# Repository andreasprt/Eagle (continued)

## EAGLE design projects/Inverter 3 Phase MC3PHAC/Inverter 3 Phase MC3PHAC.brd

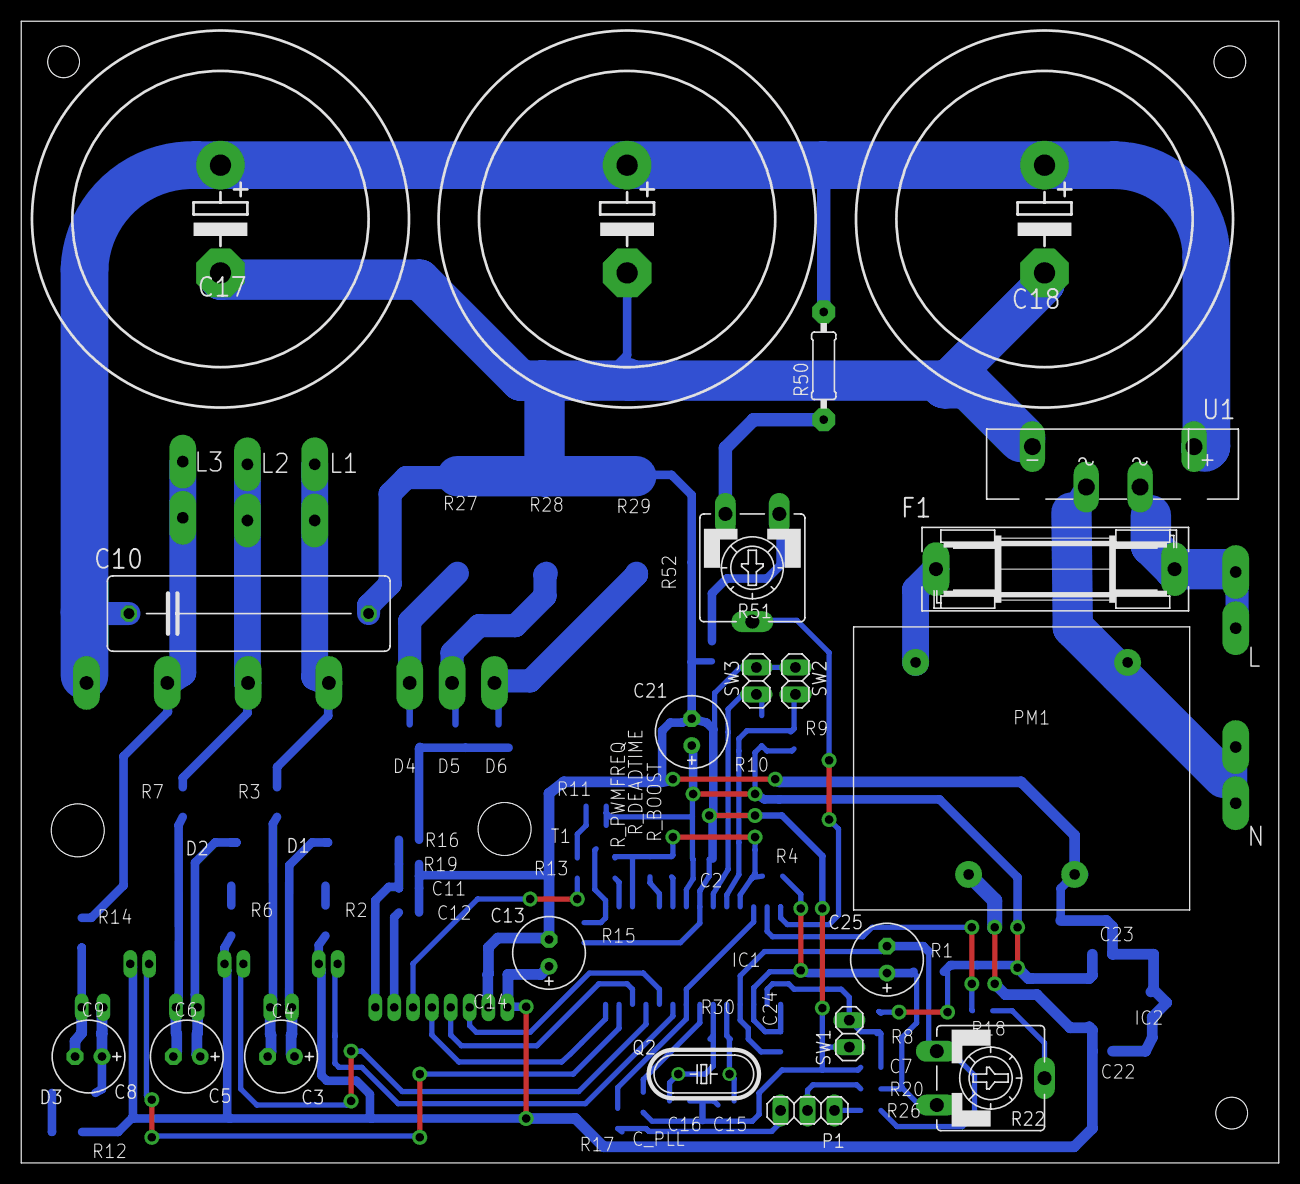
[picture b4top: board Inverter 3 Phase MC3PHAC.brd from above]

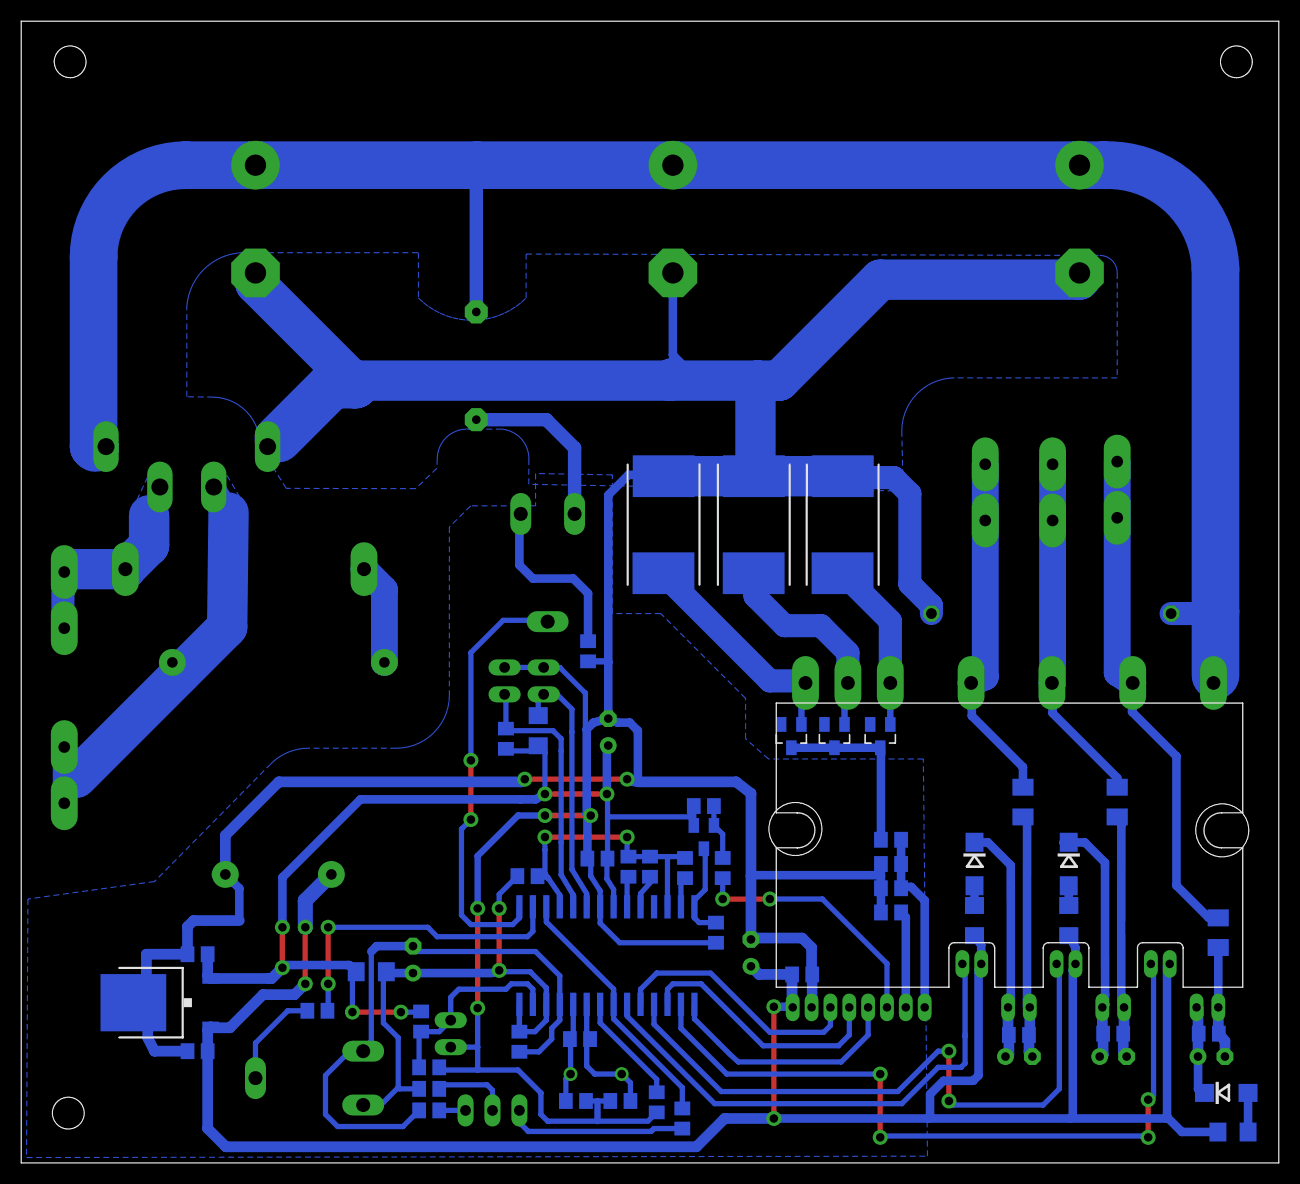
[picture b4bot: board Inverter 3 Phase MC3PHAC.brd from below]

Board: 2 copper layers, 118.6 x 107.7 mm, 78 parts (52 on the bottom side), 55 nets.

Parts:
C2, C4, C6, C7, C9, C12, C14, C22, C23, C24: 100n; C0805
C3, C5, C8, C13: 100u; E2,5-7
C10: 0.1u; C225-074X268
C11: 1n; C0805
C15, C16: 22p; C0805
C17, C18, C19: 470u; EB35D
C21: 10u; E2,5-7
C25: 1u; E2,5-7
C_PLL: 100n; C0805
D1, D2, D3: ER1J; DO214AC
D4, D5, D6: BAR43; SOT23
F1: T1A; SH22,5
IC1: MC3PHAC; SO28W
IC2: 7805DT; TO252
L, L1, L2, L3: PIN2F061.060; F061.060
N: PIN2F061.060; F061.060
P1: 5k; 1X03
PM1: MYRRA 47155; MYRRA
Q2: 4.0MHz; HC49U-V
R1: 2R; R1206
R2, R6, R12: 20R; R1206
R3, R7, R14: 5R6; M1206
R4: 6.8k; R0805
R8, R9, R15, R52: 10k; R0805
R10: 10k; R1206
R11: 6k8; R0805
R13: 22k; R0805
R16: 1k; R0805
R17, R18: 4.7k; R0805
R19: 47k; R0805
R20: 2k2; R0805
R22, R51: 4k7; CA9V
R26: 150R; R0805
R27, R28, R29: 0R082 5W; WSC4527
R30: 10M; R0805
R50: 1M; 0207/10
R_BOOST: 2k2; R0805
R_DEADTIME: 1k8; R0805
R_PWMFREQ: 3k9; R0805
SPM1: FSBS10CH60; SPM27-BA
SW1: RESET; 1X02
SW2: START; 1X02
SW3: FOR/REW; 1X02
T1: BC858; SOT23-BEC
U1: KBU8G; KBU

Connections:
+5V: C2.2, C21.+, C23.2, IC1.21, IC2.2, R1.2, R8.1, R9.1, R10.1, R11.1, T1.E
+15V: C13.+, C14.2, C22.2, IC2.1, PM1.7, R2.1, R6.1, R12.1, SPM1.1, SPM1.10, SPM1.14, SPM1.18
DC_BUS: C10.1, C17.+, C18.+, C19.+, R50.2, SPM1.27, U1.+
GND: C2.1, C7.2, C10.2, C11.1, C12.1, C13.-, C14.1, C15.1, C16.1, C17.-, C18.-, C19.-, C21.-, C22.1, C23.1, C_PLL.2, IC1.22, IC2.3, PM1.9, R15.2, R19.2, R27.1, R28.1, R29.1, R52.2, SPM1.2, SW1.1, SW2.1, SW3.1, U1.-
GND1: C24.1, C25.-, IC1.4, R22.A, R26.2
unnamed: C_PLL.1, IC1.7
unnamed: R18.2, R22.S
unnamed: IC1.16, R_PWMFREQ.2
unnamed: IC1.19, R_DEADTIME.2
unnamed: IC1.20, R_BOOST.2
unnamed: IC1.17, IC1.25, R4.1, R_BOOST.1, R_DEADTIME.1, R_PWMFREQ.1
unnamed: IC1.8, IC1.26, R17.1
unnamed: P1.3, R17.2
unnamed: C15.2, IC1.5, Q2.2, R30.2
unnamed: P1.2, R20.2
unnamed: IC1.27, R18.1
unnamed: IC1.24, R9.2, SW2.2
unnamed: IC1.23, R10.2, SW3.2
unnamed: C16.2, IC1.6, Q2.1, R30.1
unnamed: C7.1, IC1.2, R8.2, SW1.2
unnamed: N.A1, PM1.1, U1.AC2
unnamed: C5.-, C6.2, R7.2, SPM1.16
unnamed: F1.2, PM1.5
unnamed: F1.1, L.A1, U1.AC1
unnamed: R51.A, R52.1
unnamed: C3.+, C4.1, D1.C, SPM1.11
unnamed: C3.-, C4.2, R3.2, SPM1.12
unnamed: D1.A, R2.2
unnamed: C11.2, R16.2, R19.1, SPM1.8
unnamed: IC1.15, R15.1, T1.C
unnamed: C12.2, SPM1.7
unnamed: C5.+, C6.1, D2.C, SPM1.15
unnamed: D2.A, R6.2
unnamed: C8.+, C9.1, D3.C, SPM1.19
unnamed: D3.A, R12.2
unnamed: C8.-, C9.2, R14.2, SPM1.20
unnamed: D4.1, R27.2, SPM1.23
unnamed: D5.1, R28.2, SPM1.22
unnamed: D6.1, R29.2, SPM1.21
unnamed: D4.3, D5.3, D6.3, R16.1
unnamed: R11.2, R13.1, T1.B
unnamed: P1.1, R26.1
unnamed: IC1.28, R51.S
PWM-U-BOT: IC1.10, SPM1.3
PWM-U-TOP: IC1.9, SPM1.9
PWM-V-BOT: IC1.12, SPM1.4
PWM-V-TOP: IC1.11, SPM1.13
PWM-W-BOT: IC1.14, SPM1.5
PWM-W-TOP: IC1.13, SPM1.17
S$1: R50.1, R51.E
U: L1.A1, R3.1, SPM1.24
V: L2.A1, R7.1, SPM1.25
VDD: C24.2, C25.+, IC1.1, IC1.3, R1.1, R4.2, R20.1, R22.E
V_FO: R13.2, SPM1.6
W: L3.A1, R14.1, SPM1.26

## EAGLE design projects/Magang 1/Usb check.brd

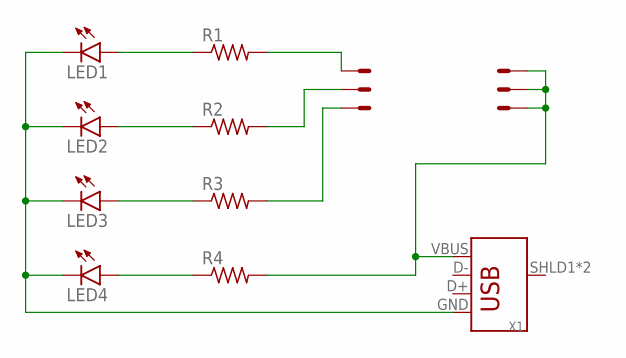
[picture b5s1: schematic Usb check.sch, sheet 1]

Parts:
LED1, LED2, LED3, LED4: LED5MM
R1, R2, R3, R4: R-US_0207/10; 0207/10
X1: USB_A_PTH_MALE; USB-A-H
X2, X3: 22-23-2031

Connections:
GND: LED1.K (C), LED2.K (C), LED3.K (C), LED4.K (C), X1.GND
unnamed: LED1.A, R1.1
unnamed: LED2.A, R2.1
unnamed: LED3.A, R3.1
unnamed: LED4.A, R4.1
unnamed: R1.2, X2.1
unnamed: R2.2, X2.2
unnamed: R3.2, X2.3
unnamed: R4.2, X1.VBUS, X3.1, X3.2, X3.3

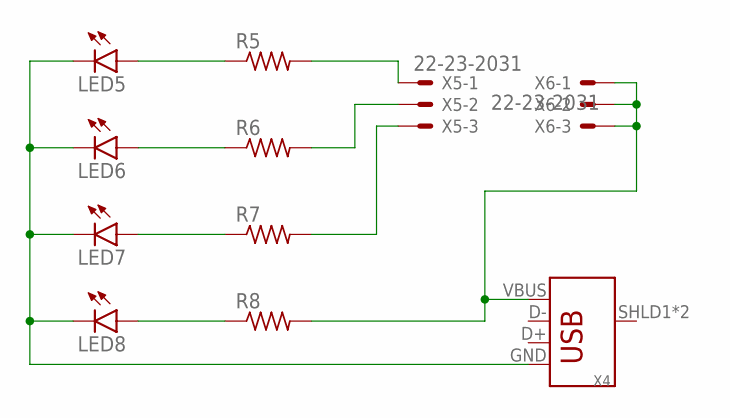
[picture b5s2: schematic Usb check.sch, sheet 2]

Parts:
LED5, LED6, LED7, LED8: LED5MM
R5, R6, R7, R8: R-US_0207/10; 0207/10
X4: USB_A_PTH_MALE; USB-A-H
X5, X6: 22-23-2031

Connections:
GND1: LED5.K (C), LED6.K (C), LED7.K (C), LED8.K (C), X4.GND
unnamed: LED5.A, R5.1
unnamed: LED6.A, R6.1
unnamed: LED7.A, R7.1
unnamed: LED8.A, R8.1
unnamed: R5.2, X5.1
unnamed: R6.2, X5.2
unnamed: R7.2, X5.3
unnamed: R8.2, X4.VBUS, X6.1, X6.2, X6.3

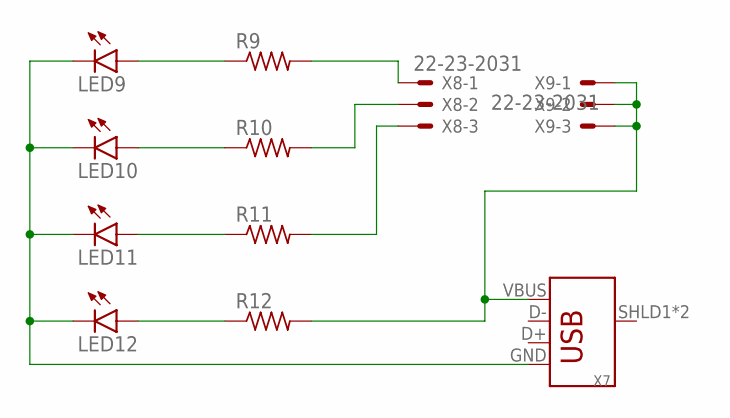
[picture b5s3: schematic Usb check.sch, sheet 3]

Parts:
LED9, LED10, LED11, LED12: LED5MM
R9, R10, R11, R12: R-US_0207/10; 0207/10
X7: USB_A_PTH_MALE; USB-A-H
X8, X9: 22-23-2031

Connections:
GND2: LED9.K (C), LED10.K (C), LED11.K (C), LED12.K (C), X7.GND
unnamed: LED9.A, R9.1
unnamed: LED10.A, R10.1
unnamed: LED11.A, R11.1
unnamed: LED12.A, R12.1
unnamed: R9.2, X8.1
unnamed: R10.2, X8.2
unnamed: R11.2, X8.3
unnamed: R12.2, X7.VBUS, X9.1, X9.2, X9.3

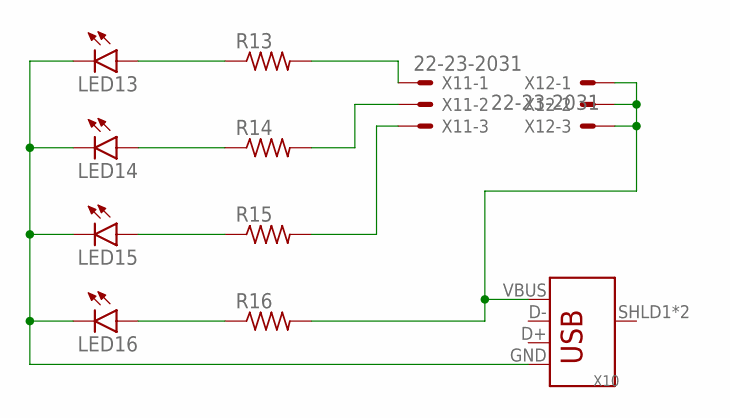
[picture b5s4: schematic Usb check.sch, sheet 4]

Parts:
LED13, LED14, LED15, LED16: LED5MM
R13, R14, R15, R16: R-US_0207/10; 0207/10
X10: USB_A_PTH_MALE; USB-A-H
X11, X12: 22-23-2031

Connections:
GND3: LED13.K (C), LED14.K (C), LED15.K (C), LED16.K (C), X10.GND
unnamed: LED13.A, R13.1
unnamed: LED14.A, R14.1
unnamed: LED15.A, R15.1
unnamed: LED16.A, R16.1
unnamed: R13.2, X11.1
unnamed: R14.2, X11.2
unnamed: R15.2, X11.3
unnamed: R16.2, X10.VBUS, X12.1, X12.2, X12.3

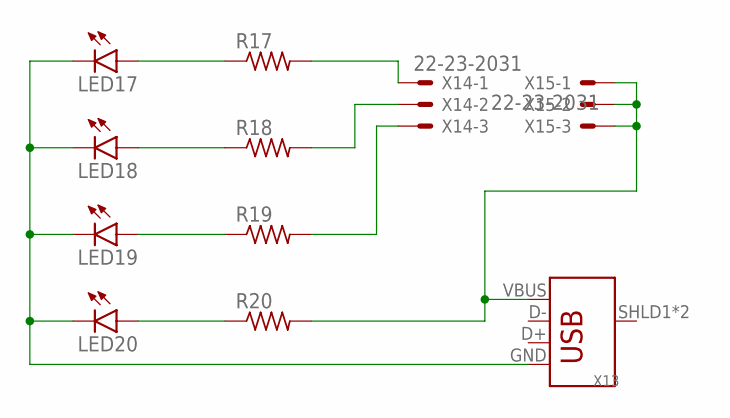
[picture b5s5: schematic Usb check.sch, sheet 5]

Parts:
LED17, LED18, LED19, LED20: LED5MM
R17, R18, R19, R20: R-US_0207/10; 0207/10
X13: USB_A_PTH_MALE; USB-A-H
X14, X15: 22-23-2031

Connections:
GND4: LED17.K (C), LED18.K (C), LED19.K (C), LED20.K (C), X13.GND
unnamed: LED17.A, R17.1
unnamed: LED18.A, R18.1
unnamed: LED19.A, R19.1
unnamed: LED20.A, R20.1
unnamed: R17.2, X14.1
unnamed: R18.2, X14.2
unnamed: R19.2, X14.3
unnamed: R20.2, X13.VBUS, X15.1, X15.2, X15.3

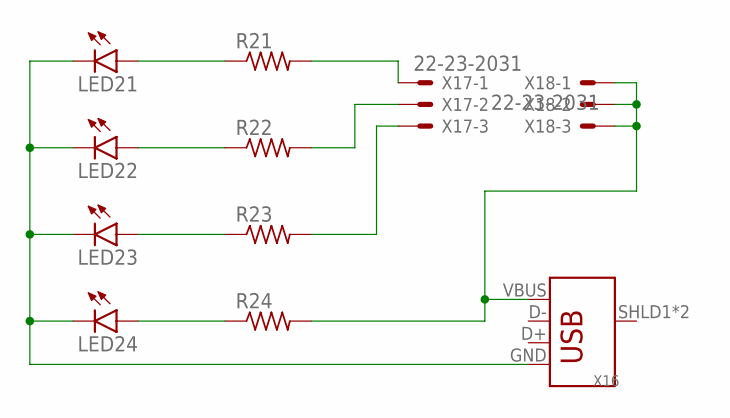
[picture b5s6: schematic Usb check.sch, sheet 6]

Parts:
LED21, LED22, LED23, LED24: LED5MM
R21, R22, R23, R24: R-US_0207/10; 0207/10
X16: USB_A_PTH_MALE; USB-A-H
X17, X18: 22-23-2031

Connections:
GND5: LED21.K (C), LED22.K (C), LED23.K (C), LED24.K (C), X16.GND
unnamed: LED21.A, R21.1
unnamed: LED22.A, R22.1
unnamed: LED23.A, R23.1
unnamed: LED24.A, R24.1
unnamed: R21.2, X17.1
unnamed: R22.2, X17.2
unnamed: R23.2, X17.3
unnamed: R24.2, X16.VBUS, X18.1, X18.2, X18.3

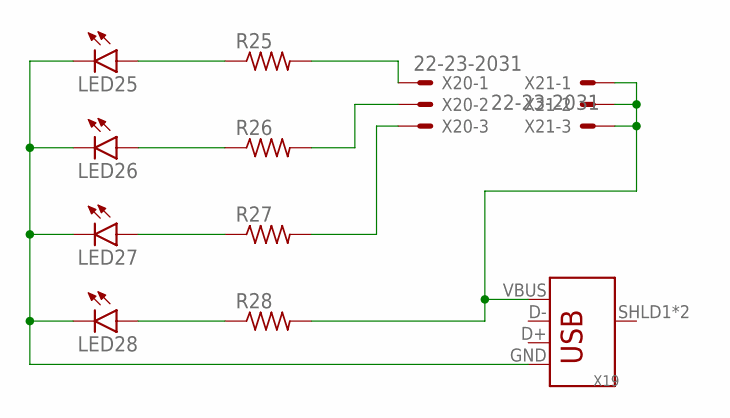
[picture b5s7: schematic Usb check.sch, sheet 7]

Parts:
LED25, LED26, LED27, LED28: LED5MM
R25, R26, R27, R28: R-US_0207/10; 0207/10
X19: USB_A_PTH_MALE; USB-A-H
X20, X21: 22-23-2031

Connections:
GND6: LED25.K (C), LED26.K (C), LED27.K (C), LED28.K (C), X19.GND
unnamed: LED25.A, R25.1
unnamed: LED26.A, R26.1
unnamed: LED27.A, R27.1
unnamed: LED28.A, R28.1
unnamed: R25.2, X20.1
unnamed: R26.2, X20.2
unnamed: R27.2, X20.3
unnamed: R28.2, X19.VBUS, X21.1, X21.2, X21.3

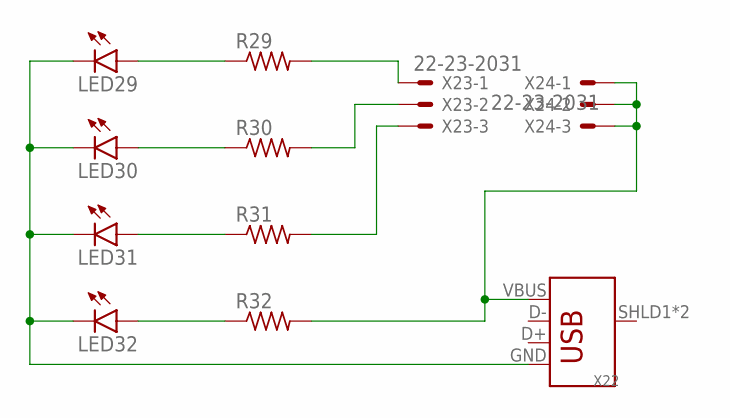
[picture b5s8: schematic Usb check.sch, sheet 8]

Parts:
LED29, LED30, LED31, LED32: LED5MM
R29, R30, R31, R32: R-US_0207/10; 0207/10
X22: USB_A_PTH_MALE; USB-A-H
X23, X24: 22-23-2031

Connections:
GND7: LED29.K (C), LED30.K (C), LED31.K (C), LED32.K (C), X22.GND
unnamed: LED29.A, R29.1
unnamed: LED30.A, R30.1
unnamed: LED31.A, R31.1
unnamed: LED32.A, R32.1
unnamed: R29.2, X23.1
unnamed: R30.2, X23.2
unnamed: R31.2, X23.3
unnamed: R32.2, X22.VBUS, X24.1, X24.2, X24.3

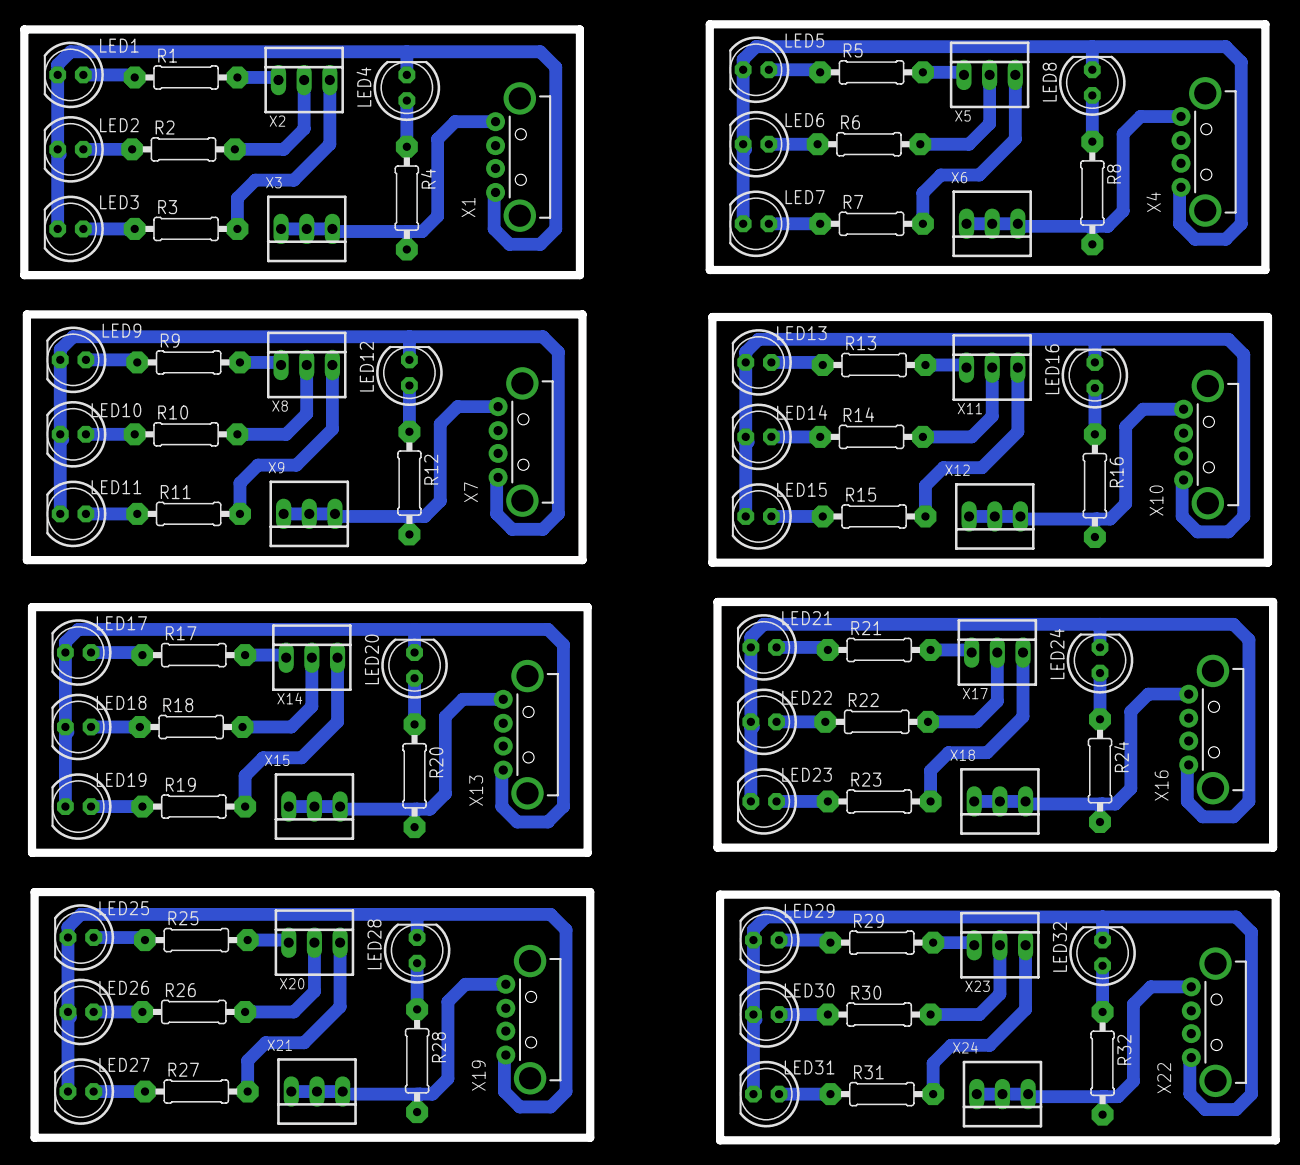
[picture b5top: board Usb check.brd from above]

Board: 2 copper layers, 123.8 x 110.4 mm, 88 parts (0 on the bottom side), 72 nets.

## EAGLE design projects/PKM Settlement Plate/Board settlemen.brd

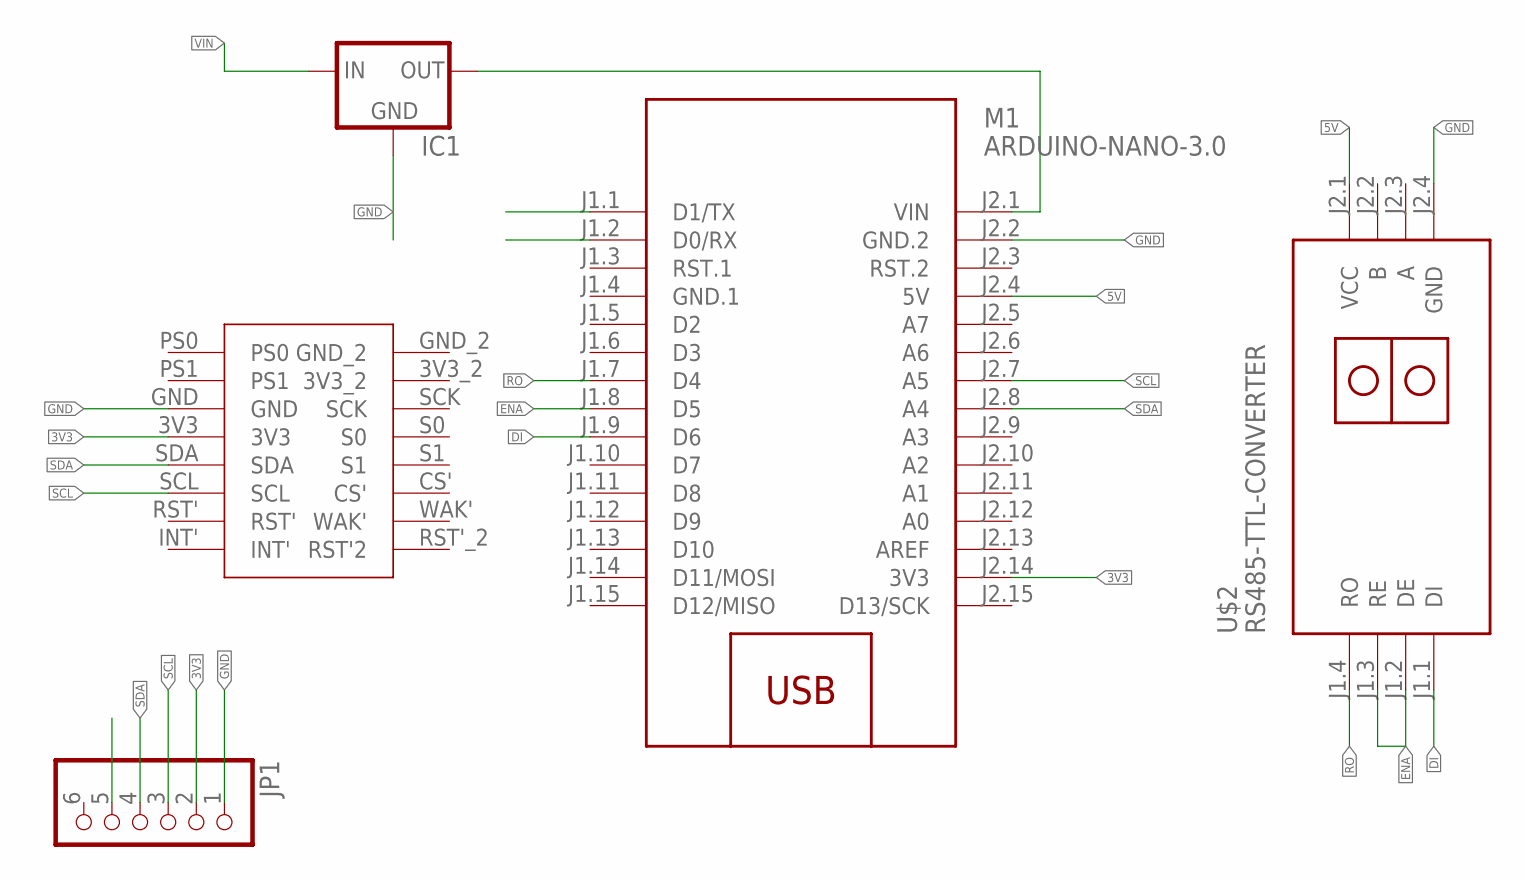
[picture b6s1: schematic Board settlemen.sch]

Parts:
IC1: 78MXXS
JP1: PINHD-1X6; 1X06
M1: ARDUINO-NANO-3.0
U$1: BNO080
U$2: RS485-TTL-CONVERTER

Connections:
3V3: JP1.2, M1.J2.14 (3V3), U$1.3V3
5V: M1.J2.4 (5V), U$2.J2.1 (VCC)
DI: M1.J1.9 (D6), U$2.J1.1 (DI)
ENA: M1.J1.8 (D5), U$2.J1.2 (DE), U$2.J1.3 (RE)
GND: IC1.GND, JP1.1, M1.J2.2 (GND.2), U$1.GND, U$2.J2.4 (GND)
GND.1: M1.J1.4 (GND.1)
unnamed: IC1.OUT, M1.J2.1 (VIN)
RO: M1.J1.7 (D4), U$2.J1.4 (RO)
SCL: JP1.3, M1.J2.7 (A5), U$1.SCL
SDA: JP1.4, M1.J2.8 (A4), U$1.SDA
VIN: IC1.IN

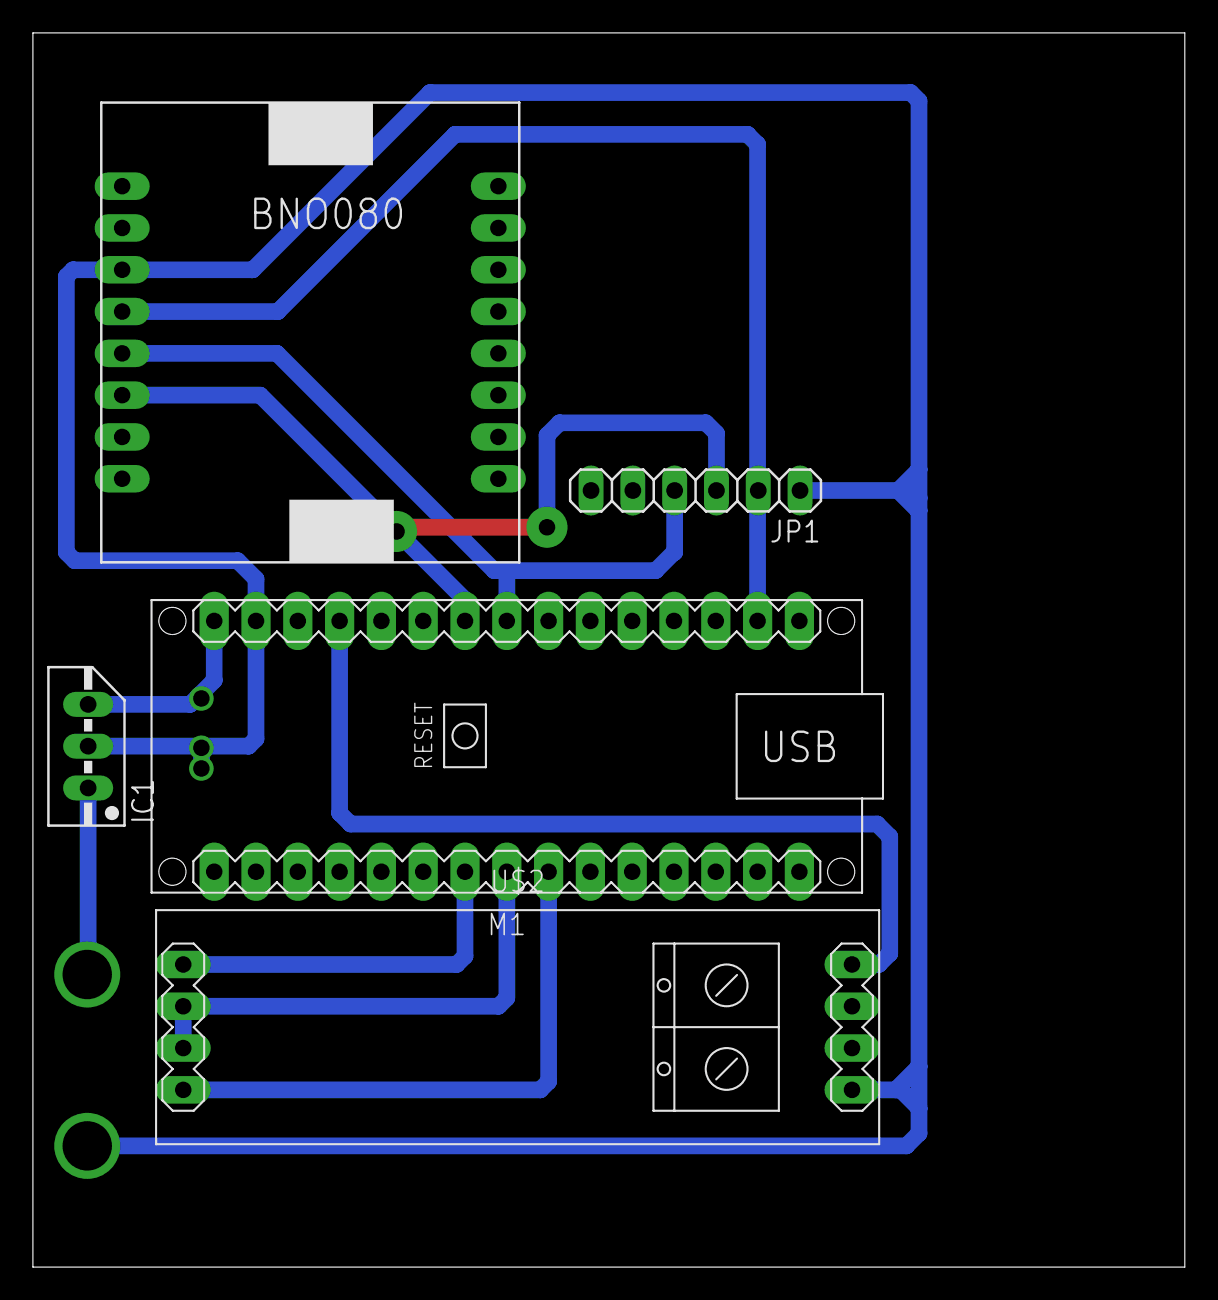
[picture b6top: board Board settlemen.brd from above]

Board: 2 copper layers, 70.0 x 75.0 mm, 5 parts (0 on the bottom side), 9 nets.

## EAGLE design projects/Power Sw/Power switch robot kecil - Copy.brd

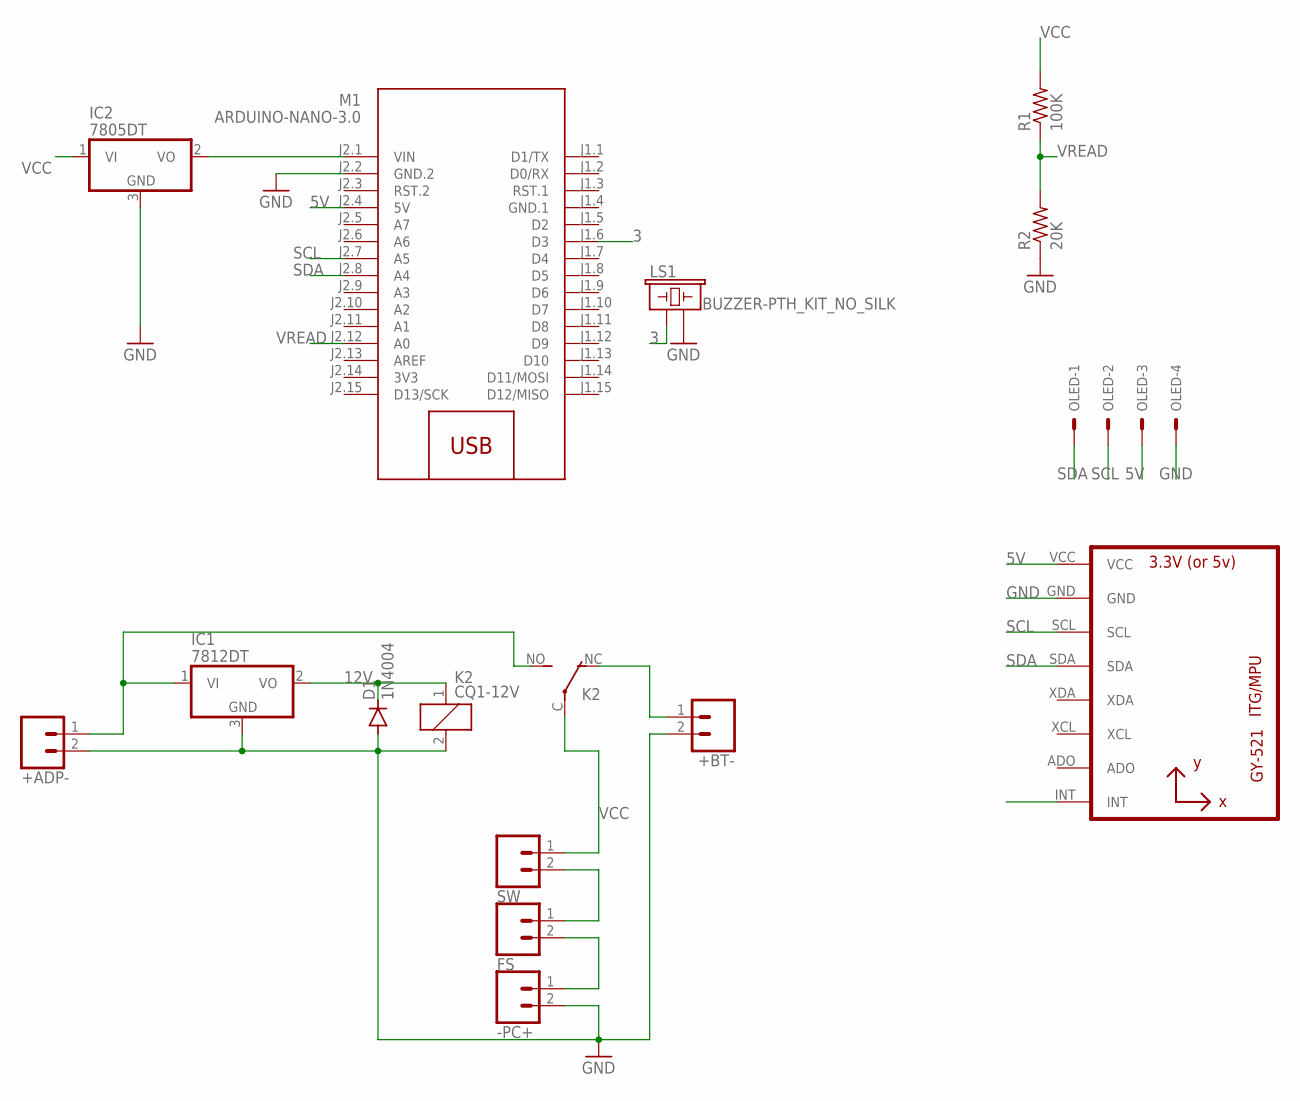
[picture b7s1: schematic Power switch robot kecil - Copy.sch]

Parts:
+ADP-: CONN_02LOCK_LONGPADS; 1X02_LOCK_LONGPADS
+BT-: CONN_02LOCK_LONGPADS; 1X02_LOCK_LONGPADS
-PC+: CONN_02LOCK_LONGPADS; 1X02_LOCK_LONGPADS
D1: 1N4004; DO41-10
FS: CONN_02LOCK_LONGPADS; 1X02_LOCK_LONGPADS
IC1: 7812DT; TO252
IC2: 7805DT; TO252
K2: CQ1-12V; CQ1
LS1: BUZZER-PTH_KIT_NO_SILK; BUZZER-12MM-NS-KIT
M1: ARDUINO-NANO-3.0
OLED: 22-27-2041-04; 6410-04
R1: 100K; 0207/10
R2: 20K; 0207/10
SW: CONN_02LOCK_LONGPADS; 1X02_LOCK_LONGPADS
U1: GY-521MPU6050; GY-521

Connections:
3: LS1.+ (1), M1.J1.6 (D3)
3V3: M1.J2.14 (3V3)
5V: M1.J2.4 (5V), OLED.3, U1.VCC
12V: D1.C, IC1.2 (VO), K2.1
GND: +ADP-.2, +BT-.2, -PC+.2, D1.A, IC1.3 (GND), IC2.3 (GND), K2.2, LS1.- (2), M1.J2.2 (GND.2), OLED.4, R2.1, U1.GND
GND.1: M1.J1.4 (GND.1)
unnamed: +ADP-.1, IC1.1 (VI), K2.NO (S)
unnamed: +BT-.1, K2.NC (O)
unnamed: -PC+.1, FS.2
unnamed: FS.1, SW.2
unnamed: IC2.2 (VO), M1.J2.1 (VIN)
SCL: M1.J2.7 (A5), OLED.2, U1.SCL
SDA: M1.J2.8 (A4), OLED.1, U1.SDA
VCC: IC2.1 (VI), K2.C, R1.2, SW.1
VREAD: M1.J2.12 (A0), R1.1, R2.2

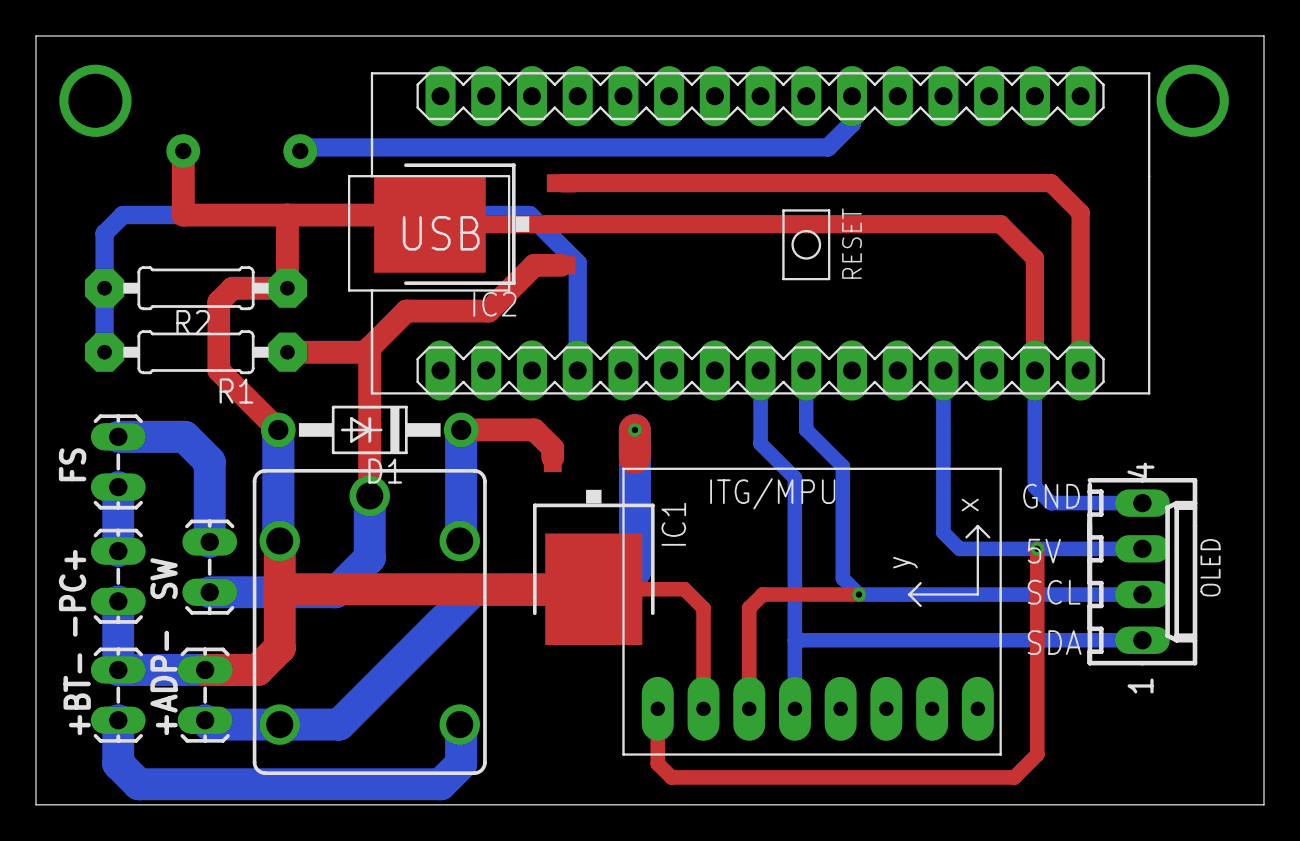
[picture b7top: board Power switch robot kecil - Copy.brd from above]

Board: 2 copper layers, 68.2 x 42.7 mm, 15 parts (0 on the bottom side), 13 nets.

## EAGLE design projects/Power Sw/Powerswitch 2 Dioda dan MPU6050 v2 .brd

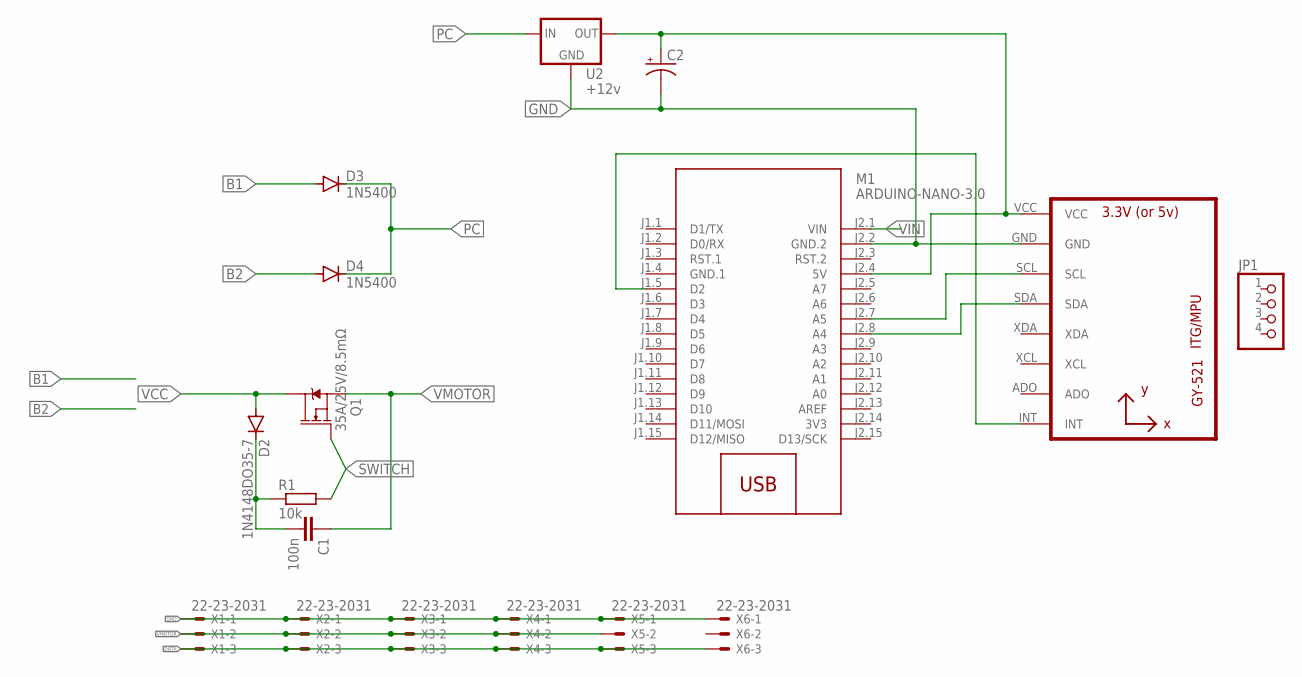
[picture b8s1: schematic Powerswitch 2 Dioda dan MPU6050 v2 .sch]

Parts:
C1: 100n; C025-030X050
C2: CPOL-USE2-5; E2-5
D2: 1N4148DO35-7; DO35-7
D3, D4: 1N5400; DO201-15
JP1: PINHD-1X4; 1X04
M1: ARDUINO-NANO-3.0
Q1: 35A/25V/8.5mΩ; DPAK
R1: 10k; R1206
U1: GY-521MPU6050; GY-521
U2: +12v; TO-252
X1, X2, X3, X4, X5, X6: 22-23-2031

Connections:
3V3: M1.J2.14 (3V3)
B1: D3.A
B2: D4.A
DATA: X1.3, X2.3, X3.3, X4.3, X5.3, X6.3
GND: C2.-, M1.J2.2 (GND.2), U1.GND, U2.3 (GND), X1.1, X2.1, X3.1, X4.1, X5.1, X6.1
GND.1: M1.J1.4 (GND.1)
unnamed: M1.J2.8 (A4), U1.SDA
unnamed: C1.2, D2.C, R1.1
unnamed: M1.J2.7 (A5), U1.SCL
unnamed: M1.J1.5 (D2), U1.INT
unnamed: C2.+, M1.J2.4 (5V), U1.VCC, U2.2 (OUT)
PC: D3.C, D4.C, U2.1 (IN)
SWITCH: Q1.1 (G), R1.2
VCC: D2.A, Q1.4 (D)
VIN: M1.J2.1 (VIN)
VMOTOR: C1.1, Q1.3 (S), X1.2, X2.2, X3.2, X4.2, X5.2

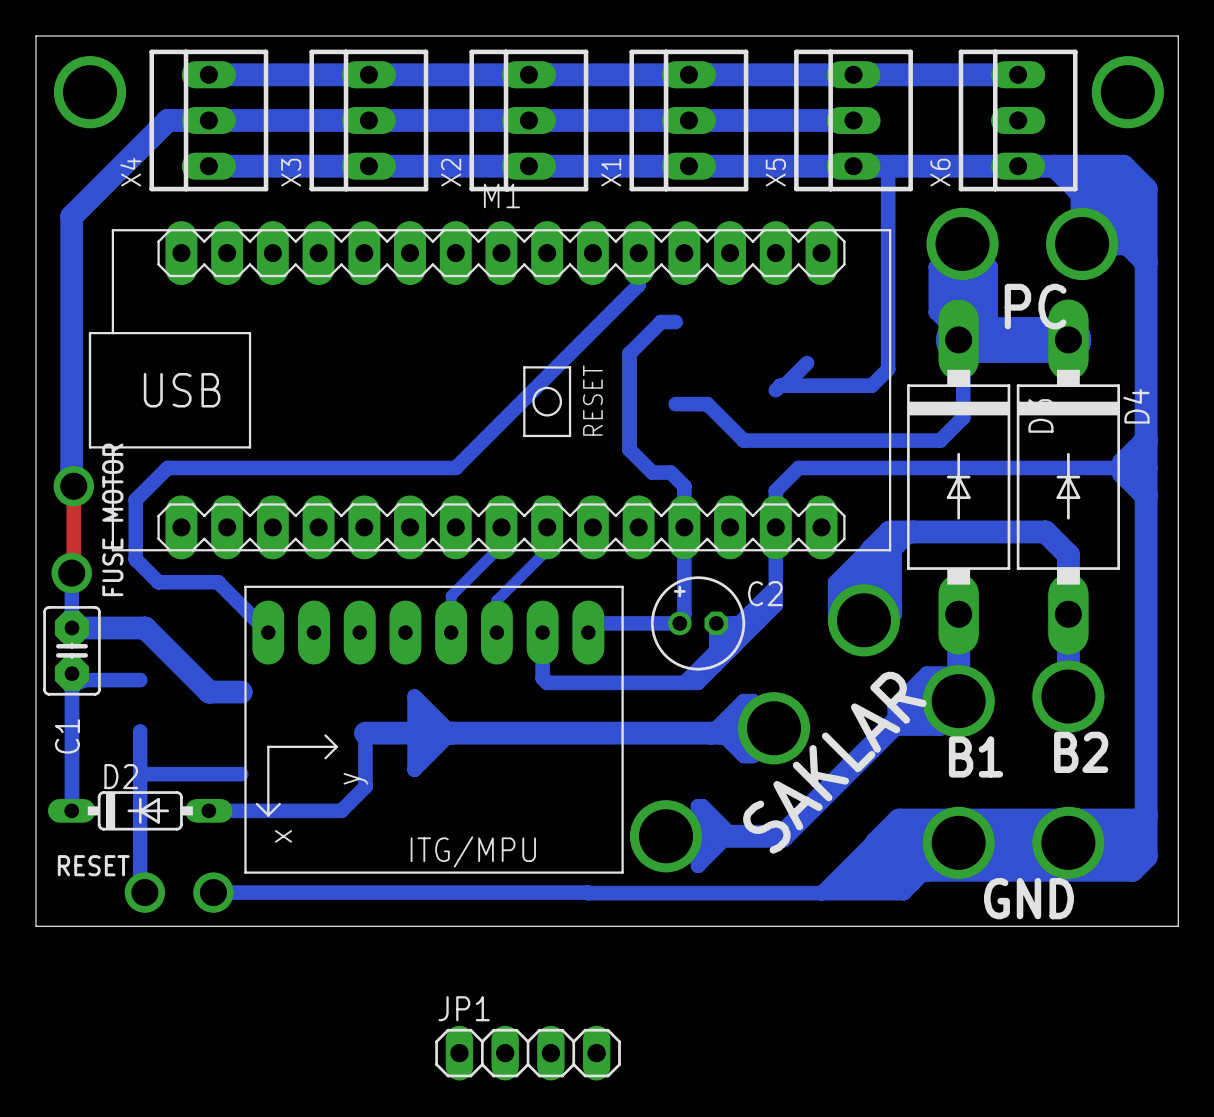
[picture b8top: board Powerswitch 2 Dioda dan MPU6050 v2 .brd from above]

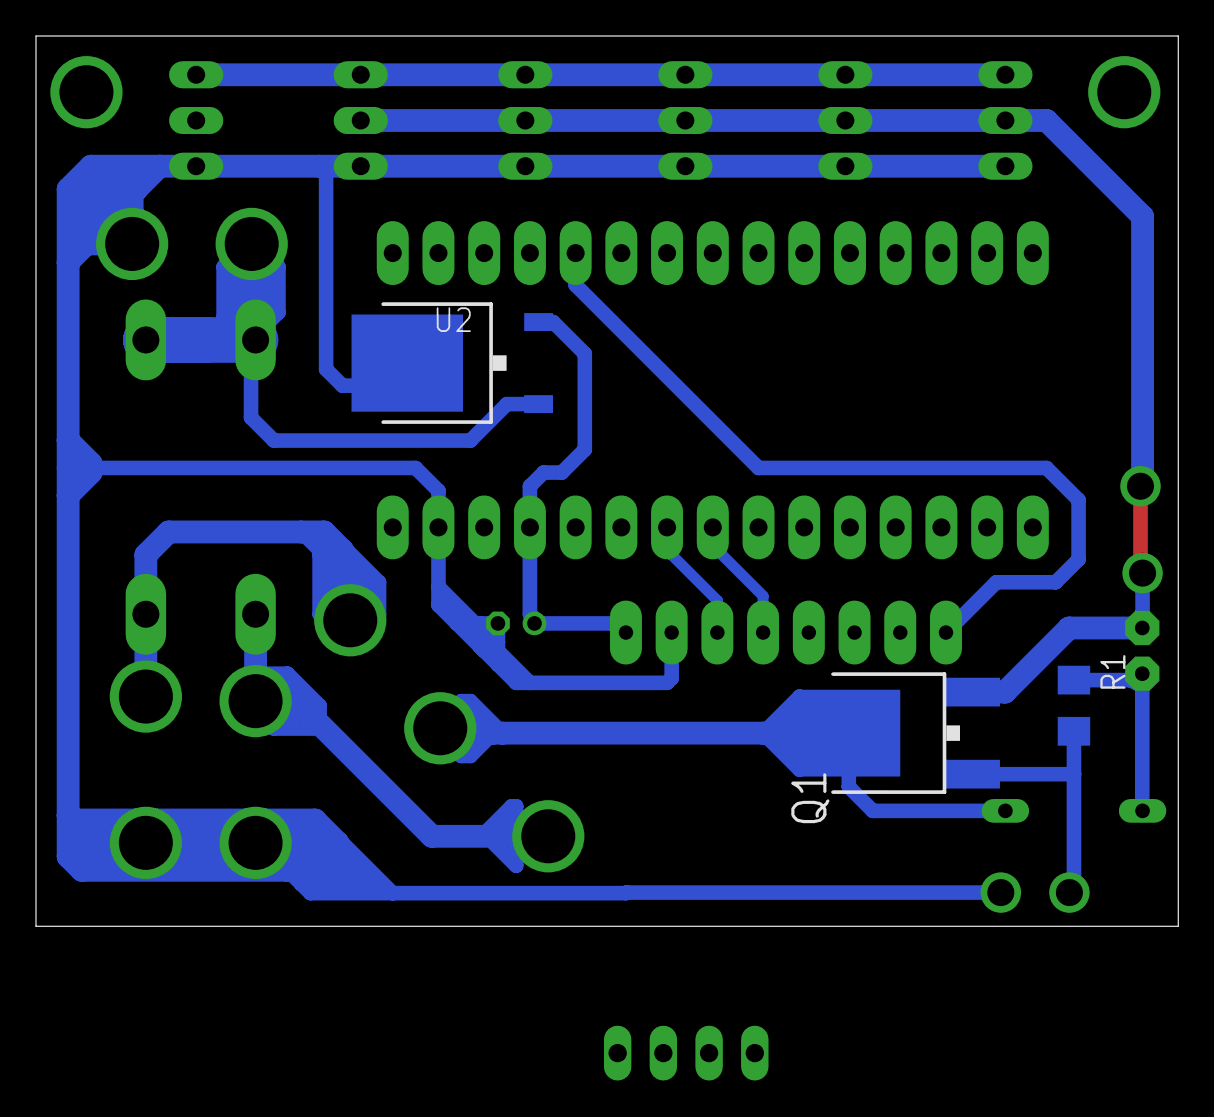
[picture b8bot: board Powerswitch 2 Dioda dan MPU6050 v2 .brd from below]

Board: 2 copper layers, 63.5 x 49.5 mm, 17 parts (3 on the bottom side), 11 nets.
